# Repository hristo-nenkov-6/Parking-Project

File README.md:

# Physical Implementation of a Garage Parking System

This repository contains the documentation, block diagrams, and schematic designs for a student project in **Digital Circuit Engineering** at the Technical University of Sofia, Plovdiv Branch.

## 👤 Author

* **Student:** Hristo Ganchev Nenkov

* **Group:** 41b group

* **Faculty Number:** 382583

* **Instructor / Evaluator:** Boris Ribov

---

## 📝 Project Overview

This project is a hardware prototype of an automated garage parking system designed for traffic control and parking space management. The system operates entirely at the hardware level using discrete logic gates (without microcontrollers). It processes input signals from entry/exit buttons to update counters and manage status indicators alongside 7-segment displays.

### Core Functionality:

* **Capacity & Counters:** The system tracks two key parameters:
* **AVAILABLE SPACES:** Initial value set to **6**. The display is designed to be placed at the entrance.

* **OCCUPIED SPACES:** Initial value set to **0**. The display is designed to be placed inside the security/guard room.

* **Button Operations:**
* `ENTER` (located outside): Pressing it upon entry decrements the *Available Spaces* counter by 1 and increments the *Occupied Spaces* counter by 1.

* `EXIT` (located inside): Pressing it upon exit increments the *Available Spaces* counter by 1 and decrements the *Occupied Spaces* counter by 1.

* `RESET / LOAD`: Reinitializes both counters to their default start values (6 available, 0 occupied).

* **Visual Indicators (LEDs):**
* 🔴 **Red LED:** Positioned under the *Available Spaces* display. Its default state is *OFF*. It turns *ON* when available spaces reach **0**, signaling that the parking lot is full.

* ⚪ **White LED:** Positioned in the center of the garage ceiling for illumination. Its default state is *ON*. It turns *OFF* when occupied spaces reach **0** since there are no cars left to illuminate.

* **Interlocking / Blocking Logic:** When the parking lot is full (*Available Spaces = 0*), the external `ENTER` button is automatically blocked to prevent false inputs. The internal `EXIT` button remains fully operational.

---

## 🛠️ Component Specification

### A) Power Supply

* **9V Battery** – Primary power source.

* **LM7805 TO-220** – Linear voltage regulator step-down to a stable +5V.

### B) Control & Signal Conditioning (Debouncing)

* **Tactile Push Button Switches** – For the Enter, Exit, and Reset triggers.

* **100nF / 200nF Capacitors** & **2.2kΩ Resistors** – Configured as RC low-pass filters.

* **IC 4093 (NAND Gate with Schmitt Trigger)** – Used for hardware debouncing to eliminate contact bounce and noise.

### C) Logic Gates & Counters

* **74HC193** – 4-bit binary up/down reversible counters.

* **IC 4093 (NAND)** & **IC 4082 (Dual 4-Input AND Gate)** – Configured to build the zero-detection (`0000`) and button-blocking combinatorial logic.

### D) Display Driver Section

* **CD4543B** – BCD to 7-segment decoder/driver (drives the *Available Spaces* display).

* **SN74LS47** – BCD to 7-segment decoder/driver (drives the *Occupied Spaces* display).

* **5161AS** – 7-segment display, **Common Anode** (for Available Spaces).

* **5161BS** – 7-segment display, **Common Cathode** (for Occupied Spaces).

* **220Ω Resistors** – Current-limiting pull-up/pull-down resistors for the display segments.

---

## 📐 Architecture & Schematics

### 1. Button Debounce Circuit

All three system buttons are hardware-stabilized using a parallel capacitor and a pull-down resistor (RC circuit). The signal passes through two inverting Schmitt triggers (4093 NAND gates with tied inputs) to output clean square pulses free of contact jitter.

### 2. System Block Diagram

```
                    [ 9V Battery ]
                          │
                  [ LM7805 (5V) ]
                          │
        ┌─────────────────┴─────────────────┐
  [ENTER Button]                      [EXIT Button]
        │                                   │
 [RC + Schmitt Filter]               [RC + Schmitt Filter]
        │                                   │
        ├─── Interlocking Logic             │
        ▼                                   ▼
 [Available Counter (74HC193)]       [Occupied Counter (74HC193)]
        │                                   │
 [Decoder CD4543B]                   [Decoder SN74LS47]
        │                                   │
 [7-Seg Common Anode]                [7-Seg Common Cathode]
        │                                   │
 [Zero-Detection Logic]              [Zero-Detection Logic]
        ▼                                   ▼
   🔴 Red LED                          ⚪ White LED

```
### 3. Video of Physal implementation
https://drive.google.com/drive/folders/18pMYzOKJq9ZjiFAOqLGpQYy0yNzwI_-t

### 4. Complete Circuit Diagram

The underlying circuit schematic is mapped out according to strict TTL/CMOS logic voltage levels. Complex checking operations—such as preventing inputs when full and evaluating counter thresholds—rely on routing the binary counter outputs (`Qa, Qb, Qc, Qd`) through combinations of `4082` AND gates and `4093` NAND gates.

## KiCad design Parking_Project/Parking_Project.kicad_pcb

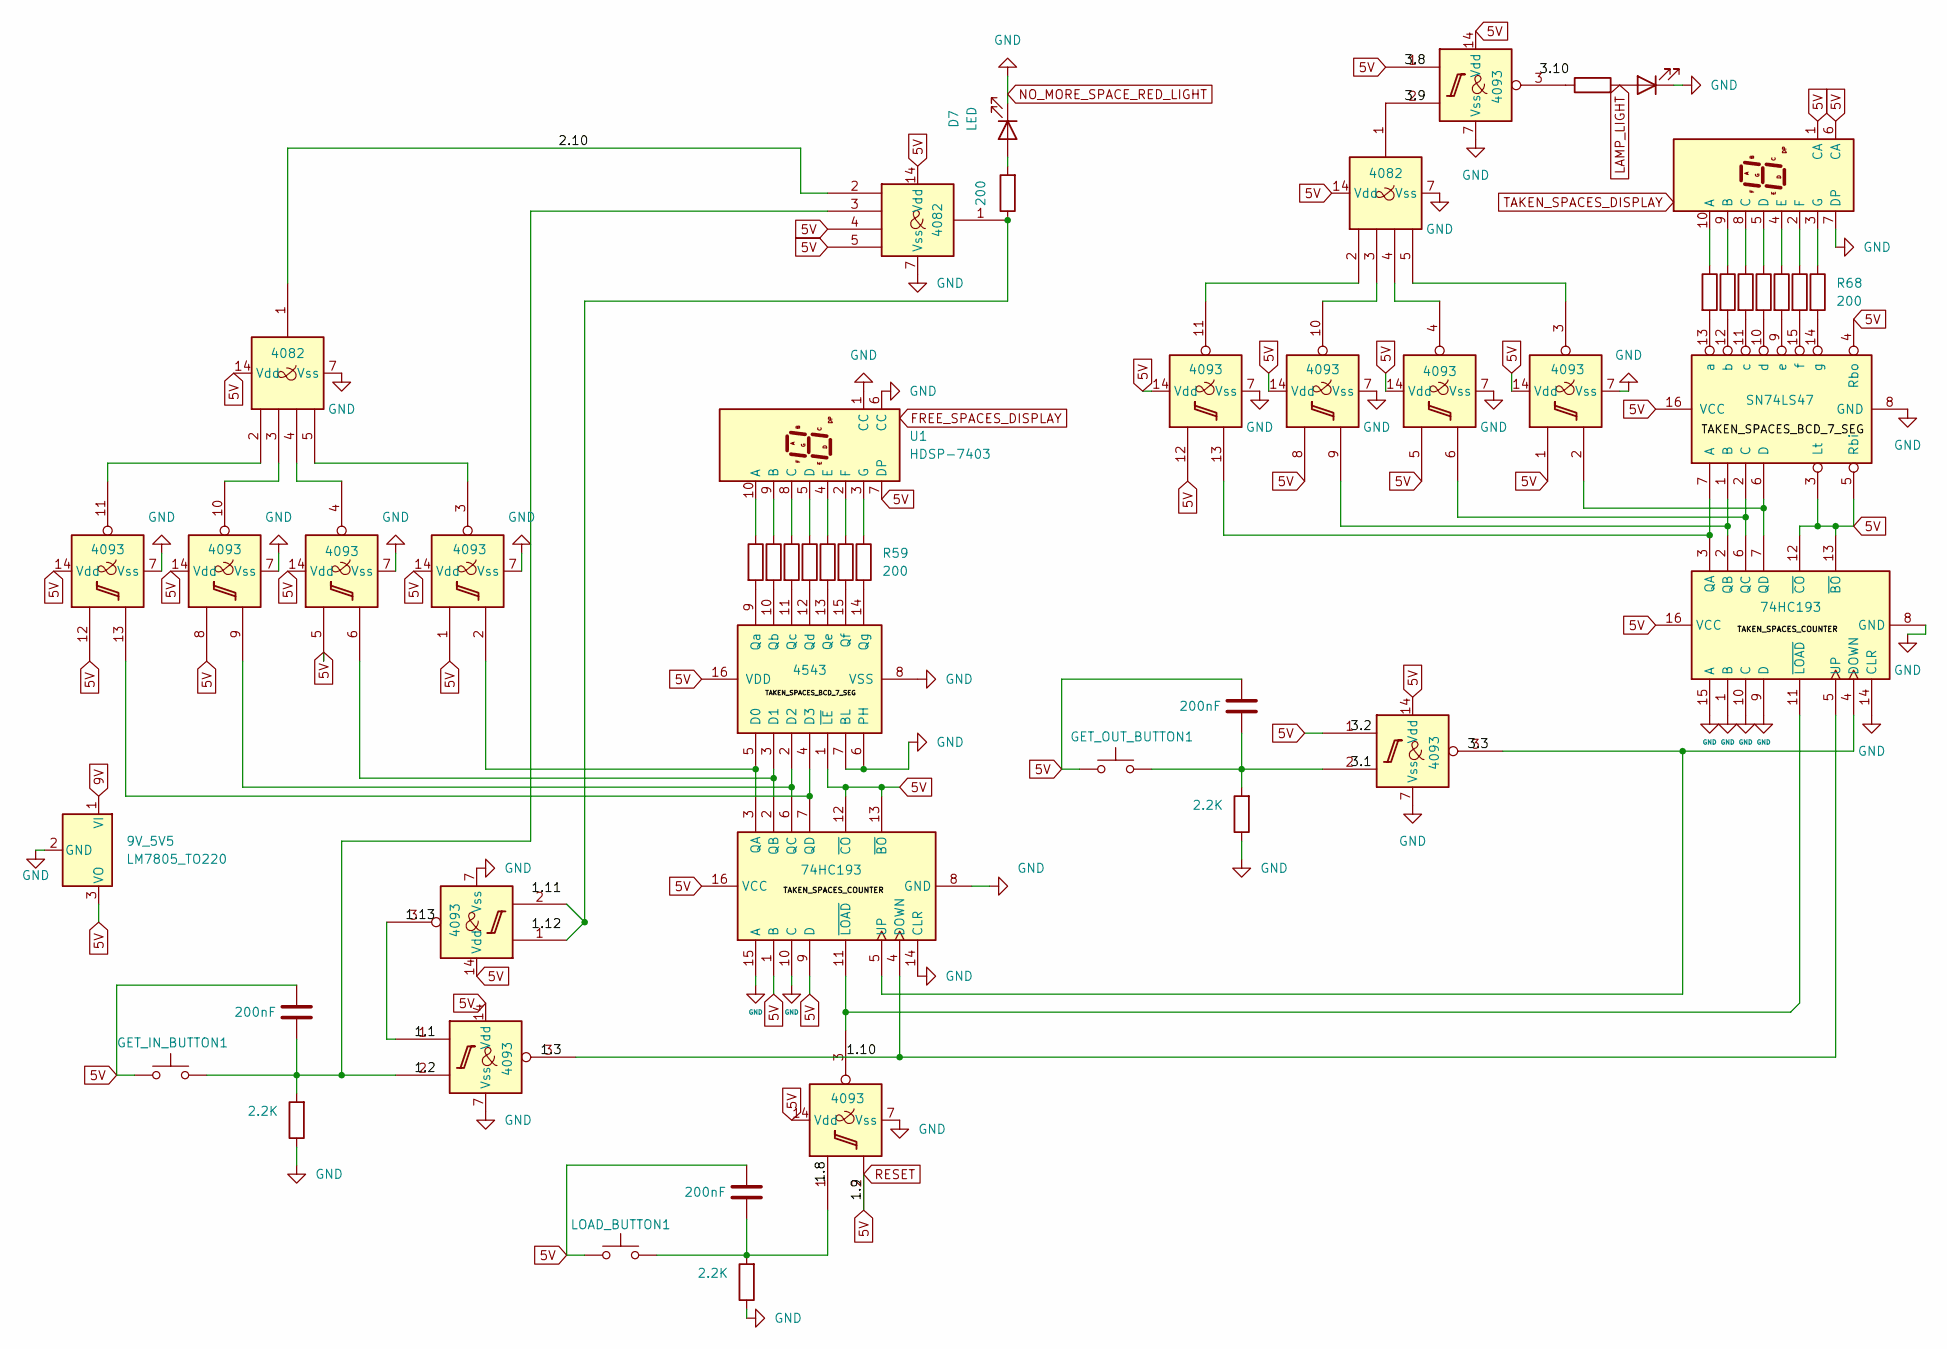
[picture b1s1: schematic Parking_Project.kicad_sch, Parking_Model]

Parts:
9V_5V5: LM7805_TO220; TO-220-3_Vertical
C10, C11, C12: 200nF; C_0201_0603Metric
D7, D8: LED; D_0201_0603Metric
GET_IN_BUTTON1: SW_Push; SW_Push_1P1T_NO_CK_KSC6xxG
GET_OUT_BUTTON1: SW_Push; SW_Push_1P1T_NO_CK_KSC6xxG
LOAD_BUTTON1: SW_Push; SW_Push_1P1T_NO_CK_KSC6xxG
R52, R60, R71: 2.2К; R_0201_0603Metric
R53, R54, R55, R56, R57, R58, R59, R62, R63, R64, R65, R66, R67, R68, R69, R70: 200; R_0201_0603Metric
U1: HDSP-7403; HDSP-7401
U2, U4, U5, U7, U8, U26, U28: 4093; DIP-14_W7.62mm
U27, U32: 74HC193; DIP-16_W7.62mm
U29, U33, U34: 4082; DIP-14_W7.62mm
U30: HDSP-7401
U31: SN74LS47; DIP-16_W7.62mm
U35: 4543; DIP-16_W7.62mm

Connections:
5V: 9V_5V5.3 (VO), C10.1, C11.1, C12.1, GET_IN_BUTTON1.1, GET_OUT_BUTTON1.1, LOAD_BUTTON1.1, U1.7 (DP), U2.14 (Vdd), U4.14 (Vdd), U5.1, U5.14 (Vdd), U7.1, U7.14 (Vdd), U8.2, U8.14 (Vdd), U26.1, U26.5, U26.8, U26.12, U26.14 (Vdd), U27.1 (B), U27.9 (D), U27.12 (~CO), U27.13 (~BO), U27.16 (VCC), U28.1, U28.5, U28.8, U28.12, U28.14 (Vdd), U29.14 (Vdd), U30.1 (CA), U30.6 (CA), U31.3 (Lt), U31.4 (Rbo), U31.5 (Rbi), U31.16 (VCC), U32.12 (~CO), U32.13 (~BO), U32.16 (VCC), U33.4, U33.5, U33.14 (Vdd), U34.14 (Vdd), U35.1 (~LE), U35.16 (VDD); also elsewhere on the board
9V: 9V_5V5.1 (VI)
/2.10: U33.2, U34.1
LAMP_LIGHT: D8.2 (A), R69.2
NO_MORE_SPACE_RED_LIGHT: 9V_5V5.2 (GND), D7.1 (K), D8.1 (K), R52.1, R60.1, R71.1, U1.1 (CC), U1.6 (CC), U2.7 (Vss), U4.7 (Vss), U5.7 (Vss), U7.7 (Vss), U8.7 (Vss), U26.7 (Vss), U27.8 (GND), U27.10 (C), U27.14 (CLR), U27.15 (A), U28.7 (Vss), U29.7 (Vss), U30.7 (DP), U31.8 (GND), U32.1 (B), U32.8 (GND), U32.9 (D), U32.10 (C), U32.14 (CLR), U32.15 (A), U33.7 (Vss), U34.7 (Vss), U35.6 (PH), U35.7 (BL), U35.8 (VSS); also elsewhere on the board
unnamed: C10.2, GET_IN_BUTTON1.2, R71.2, U2.2, U33.3
unnamed: C11.2, LOAD_BUTTON1.2, R60.2, U8.1
unnamed: C12.2, GET_OUT_BUTTON1.2, R52.2, U5.2
unnamed: D7.2 (A), R70.2
unnamed: R69.1, U7.3
unnamed: R70.1, U4.1, U4.2, U33.1
unnamed: R53.1, U1.10 (A)
unnamed: R54.1, U1.9 (B)
unnamed: R55.1, U1.8 (C)
unnamed: R56.1, U1.5 (D)
unnamed: R57.1, U1.4 (E)
unnamed: R58.1, U1.2 (F)
unnamed: R59.1, U1.3 (G)
unnamed: U2.1, U4.3
unnamed: U26.3, U34.5
unnamed: U26.4, U34.4
unnamed: U26.10, U34.3
unnamed: U26.11, U34.2
unnamed: U26.2, U27.3 (QA), U35.5 (D0)
unnamed: U26.6, U27.2 (QB), U35.3 (D1)
unnamed: U26.9, U27.6 (QC), U35.2 (D2)
unnamed: U26.13, U27.7 (QD), U35.4 (D3)
unnamed: U8.3, U27.11 (~LOAD), U32.11 (~LOAD)
unnamed: U28.3, U29.5
unnamed: U28.4, U29.4
unnamed: U28.10, U29.3
unnamed: U28.11, U29.2
unnamed: U7.2, U29.1
unnamed: R62.1, U30.10 (A)
unnamed: R63.1, U30.9 (B)
unnamed: R64.1, U30.8 (C)
unnamed: R65.1, U30.5 (D)
unnamed: R66.1, U30.4 (E)
unnamed: R67.1, U30.2 (F)
unnamed: R68.1, U30.3 (G)
unnamed: U28.13, U31.7 (A), U32.3 (QA)
unnamed: U28.9, U31.1 (B), U32.2 (QB)
unnamed: U28.6, U31.2 (C), U32.6 (QC)
unnamed: U28.2, U31.6 (D), U32.7 (QD)
unnamed: R62.2, U31.13 (a)
unnamed: R63.2, U31.12 (b)
unnamed: R64.2, U31.11 (c)
unnamed: R65.2, U31.10 (d)
unnamed: R66.2, U31.9 (e)
unnamed: R67.2, U31.15 (f)
unnamed: R68.2, U31.14 (g)
unnamed: R53.2, U35.9 (Qa)
unnamed: R54.2, U35.10 (Qb)
unnamed: R55.2, U35.11 (Qc)
unnamed: R56.2, U35.12 (Qd)
unnamed: R57.2, U35.13 (Qe)
unnamed: R58.2, U35.15 (Qf)
unnamed: R59.2, U35.14 (Qg)

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
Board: 2 copper layers, 46 parts (0 on the bottom side), 61 nets, no tracks yet.

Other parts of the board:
U3, U6: 4093; DIP-14_W7.62mm

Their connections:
5V: U3.14 (Vdd), U6.14 (Vdd); also elsewhere on the board
NO_MORE_SPACE_RED_LIGHT: U3.7 (Vss), U6.7 (Vss); also elsewhere on the board
